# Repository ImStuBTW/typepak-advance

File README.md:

# TypePak Advance

The [TypePak Advance](https://github.com/ImStuBTW/typeboy-advance) is an update to my original [TypePak](https://github.com/ImStuBTW/typeboy_and_typepak/tree/main/typepak) design from 2023. The original idea for the concept was to put as many wireless keyboard components as possible inside of the shell of a Game Boy Advance cartridge. This allows you to more easily move the microcontroller between builds, but honestly it's primarily done for aesthetic reasons. Slapping a Game Boy cartridge port and cartridge onto the side of one's keyboard takes up a decent amount of space compared to a Pro Micro or a XIAO, but it does look neat. If you're iterating through designs rapidly, it does manage to cut down on some build considerations like where to put the LiPo battery.

The original TypePak design had a few flaws. It embedded an entire XIAO nRF52840 microcontroller onto the Game Boy cartridge breakout board. This simplified things on the design side, but complicated the assembly substantially. The XIAO's USB port needed to be exposed to flash new firmware and charge the TypePak's battery, so a large chunk needed to be cut out with a Dremel. The USB port was also fairly tall, and it had a nasty habit of crushing the integrated Sharp Memory Display as one tried to slide the enclosure together. In total 3 original TypePaks have been built, and only one managed to get a working display. Finally the pinout situation is less than ideal. The XIAO is famously limited on the amount of GPIO ports it has on offer, so the original TypePak leveraged a shift register to provide a few additional column pins. This worked well enough for split keyboards, but it's still not enough for unibody designs. In hindsight I *really* should have broken out the shift register's daisy-chain pin.

This v2 attempt is seeking to clean up a few lingering issues with the TypePak. The TypePak Advance's largest changes are:
- Leveraging a bare nRF52840 module to save space and give the display more space.
- Dropping the integrated USB port entirely in favor of breaking out those pins over the edge connector. No more cartridge shell modifications!
- More pins! The TypePak Advance has 23 GPIO pins exposed in total.
    - The nRF52840's high frequency pins are grouped together with the [VIK](https://github.com/sadekbaroudi/vik) keyboard extension standard in mind. After the VIK's SPI, I2C, RGB, and 2 GPI pins, the TypePak Advance still has 14 additional pins to work with.
- Features an always-on 3v3 pin and a toggle-able software controlled 3v3 pin to allow persistent and power conscious peripherals. 

To build a TypePak Advance compatible keyboard, one would need to include a Game Boy cartridge slot, a USB port for charging and data, a power switch, and a reset button.

The TypePak Advance leveraged the [nRFMicro](https://github.com/joric/nrfmicro) project for the basis of its schematic, and owes a great deal to the project's excellent documentation. Thanks y'all! The Game Boy Cartridge PCB designs are from [KiCAD-GamePaks](https://github.com/djedditt/kicad-gamepaks).

## Pinout

The TypePak Advance offers an indulgent 32 pins on its edge connector. A minimalist XAIO this is not. Nine of these pins are reserved for power, data, and board management features, but that still leaves you with 23 pins of GPIO. From left to right, you've got:

- The USB power and data pins. These pins need to be routed to a USB socket on the main keyboard PCB. (Most likely a USB-C port, but the pins can be put into a socket shape of your choice.)
- The Reset pin. Bridge this with the GND pin and your microcontroller will restart. Bridge it twice and the nRF52840 will boot into its flashing mode. This Reset pin and the GND should be wired up to a pushbutton on the main keyboard PCB.
- 14 GPIO pins. These pins are a mixture of the nRF52840's "Low Frequency" and "High Frequency" pins. The [nRFMicro Wiki](https://github.com/joric/nrfmicro/wiki/Pinout#low-drive-pins) has a good rundown, but essentially the high frequency pins are recommended for serial communication. Six of these pins can also be used for analog inputs.
- 9 additional serial and GPIO pins laid out in a similar order as to the [VIK](https://github.com/sadekbaroudi/vik) keyboard extension standard.
    - SPI's clock, input, output, and a chip select pin. The SCK and MISO pins have already been used by the built in Sharp Memory Display. These pins can be re-used for additional SPI devices, but shouldn't be used for general keyboard GPIO.
    - 2 general purpose pins.
    - An `RGB_Out` pin intended to be used for serial-addressable RGB LEDs. If the keyboard itself features addressable RGB LEDs, this pin should continue the end of the LED chain. If the keyboard does not feature an LED chain, it can be treated as the start of an RGB strand.
    - 2 pins for I2C serial communication.
- A software controllable 3v3 pin. Power to this pin can be shutoff via a MOSFET by ZMK so that power-hungry electronics such as LEDs do not drain your keyboard's battery life. It uses the same `EXT_VCC` functionality as the Nice!Nano and nRFMicro.
- An always-on 3v3 pin. This can be used for components which you will always want on, even when battery powered. Internally it's already giving power to the nRF52840 and the Sharp Memory Display.
- The battery pins. `BAT_OUT` is the line coming straight out of the LiPo battery. It needs to be connected to the VBAT pin in order to turn on the TypePak Advance. This should be done on the main keyboard PCB via a power switch.

## Open Considerations

I'm by no means an EE, and this is my first time working with a bare E73 nRF52840. Before I send this to the fab, I'm looking into the following topics. Consider this a to-do list of items I need to verify.

### Power

The nRFMicro has `VBAT`, `VBUS`, `nRF_VDD`, `EXT_VCC`, a `POWER_PIN`, and a `BATTERY_PIN`. I need to triple-check that I didn't get these mixed up anywhere.

Typically when working with batteries I put the switch onto the battery's `GND` lead so that the power pin isn't being as futzed with as much. The nRFMicro puts the switch on the power pin however, and I don't want to mess up any of the charging circuitry by accidentally having the battery's positive lead wired up when its not supposed to.

Breaking out the toggle-able `EXT_VCC` and always-on `nRF_VDD` looks worth it on paper, but it's been a bit since I've made a wireless keyboard. I'm not sure how many builds actually feature a mixture of components one would want powered up and powered down while wireless. Keeping the display on was my largest concern. I do have some spare GPIO pins I could break out if wanted an even number of pins on the board.

### Pins

Breaking out USB over an edge connector and running the data lines for a few centimeters has to be a pretty big no-no, right? The keyboard will be talking over Bluetooth most of the time. Maybe I should at least look into putting an ESD on the keyboard's port. I don't know if also putting one on the cartridge side would be a good idea too, but I'm starting to run out of room there.

I've never built a keyboard with VIK support in mind before, but I'm trying to future-proof this keyboard a bit. It'd be neat to power a trackball or trackpad via a TypePak. VIK's pinout is: `3V3, GND, SDA, SCL, RGB, 5V, GPIO1, MOSI, GPIO2, CS, MISO, and SCLK`. This is flipped on the TypePak so that when it's wired up to the connector, all the data pins would be in the correct order. The trick is that the TypePak doesn't have the 3v3, GND, or 5V pins mixed in with the rest. For the sake of maximizing the amount of GPIO, it would need to grab the GND off of the USB pinout, one of the 3V3 pinouts (with a selectable jumper pad if you wanted to get clever about it), and then... VBUS for the 5V pin? I don't know if this would actually meet the VIK spec, but it seems like most boards are focused on 3v3 devices. Also, shoot, I just realized VIK wanted one of those Analog In pins for its two GPIOs.

I was hoping to make a large VIK compatible unibody with this keyboard at some point, but there's surprisingly not enough pins to do it without a shift register. 12 columns and 5 rows is still 16 pins even if you optimize the matrix. It doesn't seem worth it to drop the `RESET` pin and rely on the keyboard firmware's software reset feature, and only offer the toggle-able 3V3. Shift register it is!

My understanding is that any high frequency pin can be used for SPI and I2C, but I should double-check that.

Again, this will be my first time working with a bare nRF52840 module, so we'll see how the placement on those programming pins goes. Wish me luck!

### Stray Thoughts

Earlier nRFMicro boards used a timing crystal between `P0.00` and `P0.01`. It would save a bit of battery life, but I'd need to find space for it and figure out how to enable it in the firmware.

I'm not using PCBA for this keyboard, so I bumped most of the 603 SMD components up to 805 variants that should be a little easier to hand solder.

Speaking of which, I still need to assemble a proper bill of materials for this build.

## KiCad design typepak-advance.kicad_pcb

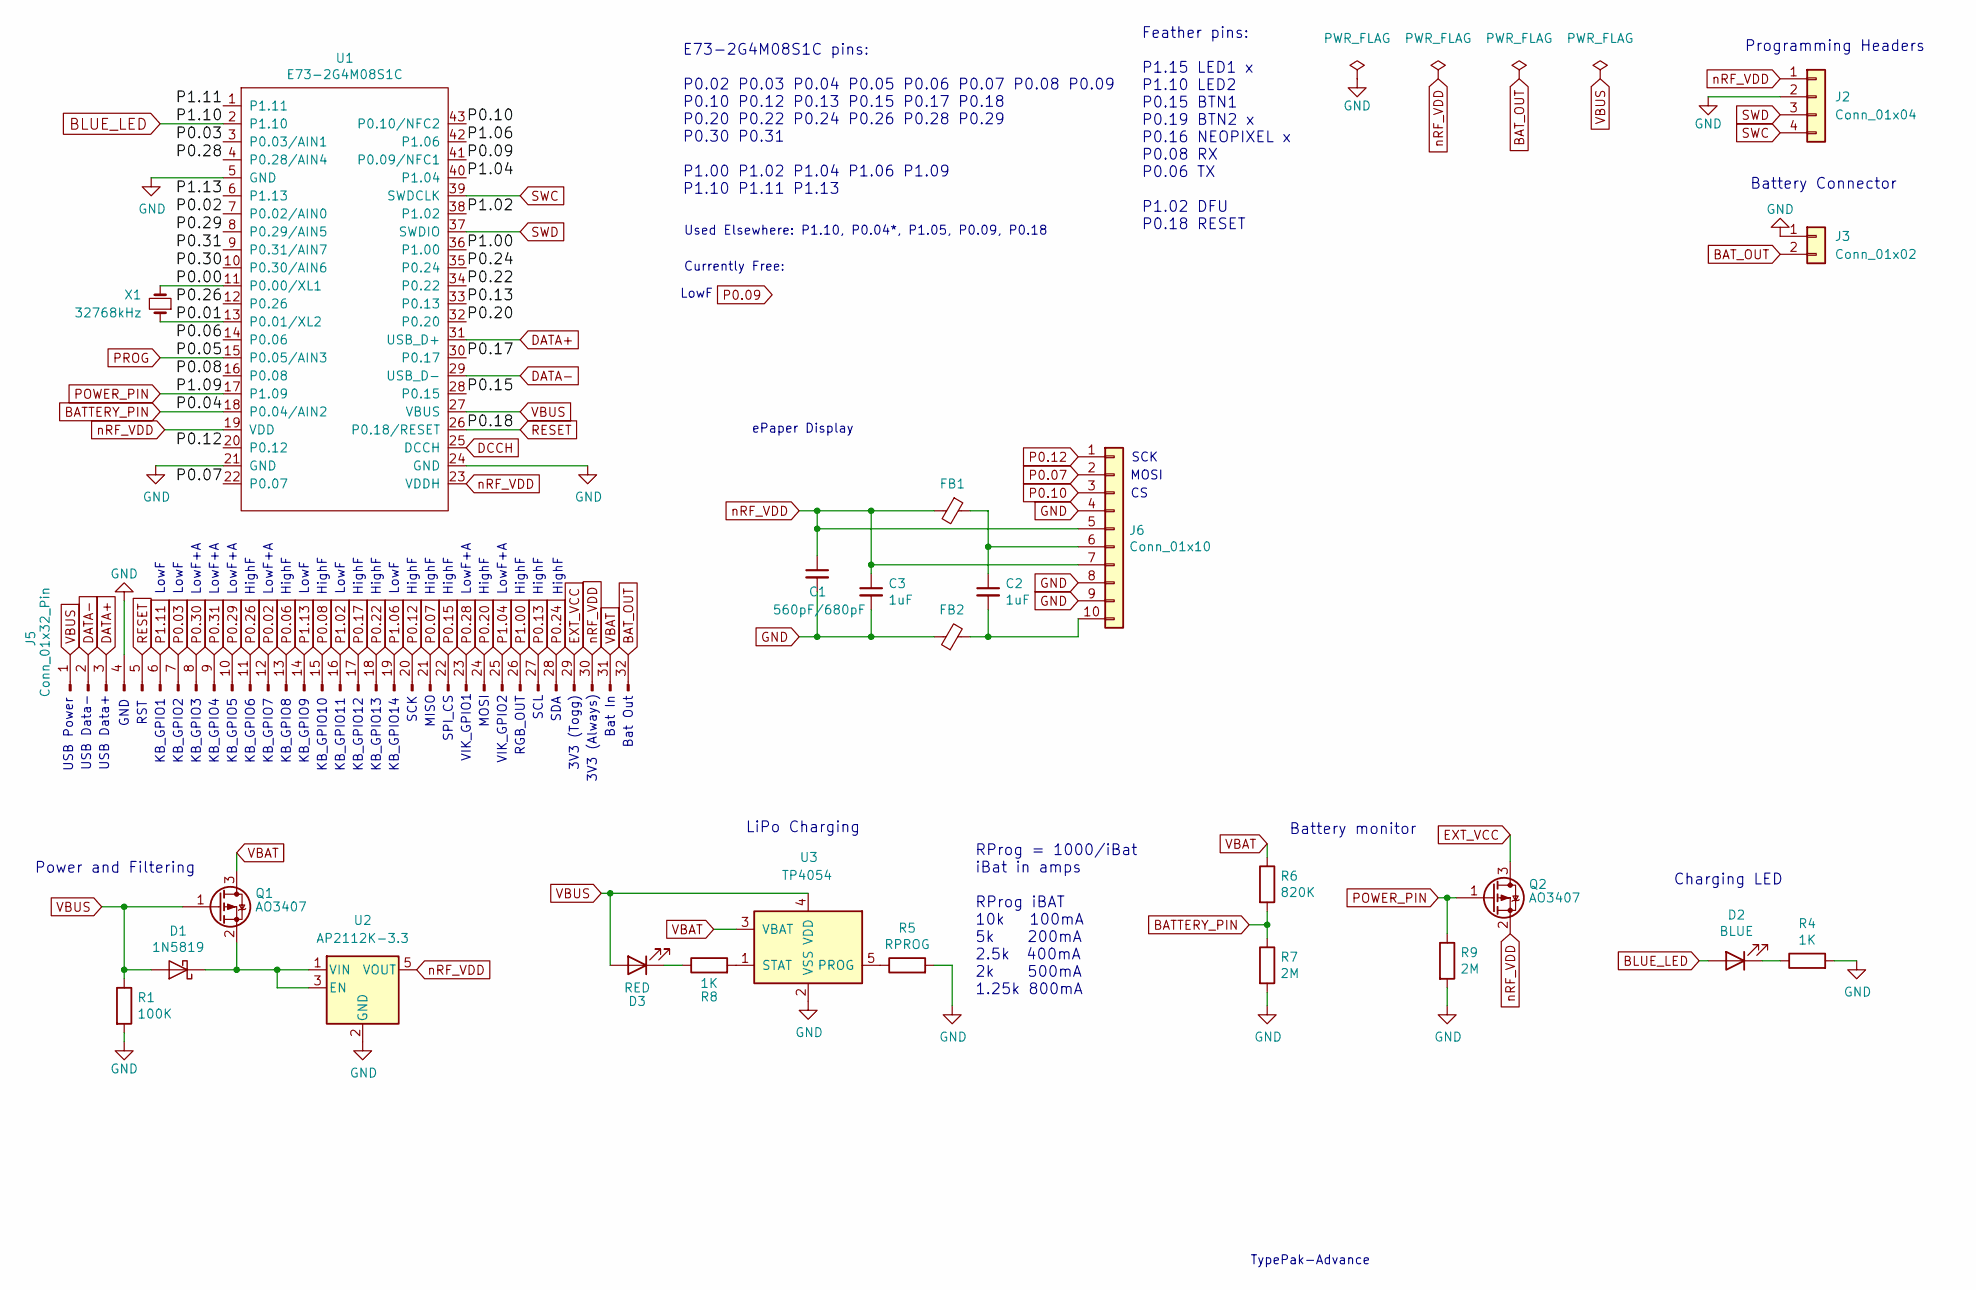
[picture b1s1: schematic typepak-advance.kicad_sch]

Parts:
C1: 560pF/680pF; C_0805_2012Metric_Pad1.18x1.45mm_HandSolder; LCSC C84721
C2, C3: 1uF; C_0805_2012Metric_Pad1.18x1.45mm_HandSolder; LCSC C15849
D1: 1N5819; D_SOD-123F
D2: BLUE; LED_0805_2012Metric_Pad1.15x1.40mm_HandSolder
D3: RED; LED_0805_2012Metric_Pad1.15x1.40mm_HandSolder
FB1, FB2: FerriteBead_Small; R_0805_2012Metric_Pad1.20x1.40mm_HandSolder
J2: Conn_01x04; connector_swd
J3: Conn_01x02
J5: Conn_01x32_Pin
J6: Conn_01x10; Hirose_FH12-10S-0.5SH_1x10-1MP_P0.50mm_Horizontal; LCSC C506791
Q1, Q2: AO3407; SOT-23_Handsoldering
R1: 100K; R_0805_2012Metric_Pad1.20x1.40mm_HandSolder
R4, R8: 1K; R_0805_2012Metric_Pad1.20x1.40mm_HandSolder
R5: RPROG; R_0805_2012Metric_Pad1.20x1.40mm_HandSolder
R6: 820K; R_0805_2012Metric_Pad1.20x1.40mm_HandSolder
R7, R9: 2M; R_0805_2012Metric_Pad1.20x1.40mm_HandSolder
U1: E73-2G4M08S1C; E73-2G4M08S1C-52840
U2: AP2112K-3.3; SOT-23-5_HandSoldering
U3: TP4054; SOT-23-5_HandSoldering
X1: 32768kHz

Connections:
/P0.00: U1.11 (P0.00/XL1), X1.2
/P0.01: U1.13 (P0.01/XL2), X1.1
BATTERY_PIN: R6.2, R7.1, U1.18 (P0.04/AIN2)
BAT_OUT: J3.2, J5.32
BLUE_LED: D2.2 (A), U1.2 (P1.10)
DATA+: J5.3, U1.31 (USB_D+)
DATA-: J5.2, U1.29 (USB_D-)
DCCH: U1.25 (DCCH)
EXT_VCC: J5.29, Q2.3 (D)
GND: C1.2, C3.2, FB2.1, J2.2, J3.1, J5.4, J6.4, J6.8, J6.9, R1.2, R4.2, R5.2, R7.2, R9.2, U1.5 (GND), U1.21 (GND), U1.24 (GND), U2.2 (GND), U3.2 (VSS)
unnamed: D1.1 (K), Q1.2 (S), U2.1 (VIN), U2.3 (EN)
unnamed: D2.1 (K), R4.1
unnamed: D3.1 (K), R8.1
unnamed: C2.1, FB1.1, J6.6
unnamed: C2.2, FB2.2, J6.10
unnamed: R5.1, U3.5 (PROG)
unnamed: R8.2, U3.1 (STAT)
P0.02: J5.12, U1.7 (P0.02/AIN0)
P0.03: J5.7, U1.3 (P0.03/AIN1)
P0.06: J5.13, U1.14 (P0.06)
P0.07: J5.21, J6.2, U1.22 (P0.07)
P0.08: J5.15, U1.16 (P0.08)
P0.09: U1.41 (P0.09/NFC1)
P0.10: J6.3, U1.43 (P0.10/NFC2)
P0.12: J5.20, J6.1, U1.20 (P0.12)
P0.13: J5.27, U1.33 (P0.13)
P0.15: J5.22, U1.28 (P0.15)
P0.17: J5.17, U1.30 (P0.17)
P0.20: J5.24, U1.32 (P0.20)
P0.22: J5.18, U1.34 (P0.22)
P0.24: J5.28, U1.35 (P0.24)
P0.26: J5.11, U1.12 (P0.26)
P0.28: J5.23, U1.4 (P0.28/AIN4)
P0.29: J5.10, U1.8 (P0.29/AIN5)
P0.30: J5.8, U1.10 (P0.30/AIN6)
P0.31: J5.9, U1.9 (P0.31/AIN7)
P1.00: J5.26, U1.36 (P1.00)
P1.02: J5.16, U1.38 (P1.02)
P1.04: J5.25, U1.40 (P1.04)
P1.06: J5.19, U1.42 (P1.06)
P1.11: J5.6, U1.1 (P1.11)
P1.13: J5.14, U1.6 (P1.13)
POWER_PIN: Q2.1 (G), R9.1, U1.17 (P1.09)
PROG: U1.15 (P0.05/AIN3)
RESET: J5.5, U1.26 (P0.18/RESET)
SWC: J2.4, U1.39 (SWDCLK)
SWD: J2.3, U1.37 (SWDIO)
VBAT: J5.31, Q1.3 (D), R6.1, U3.3 (VBAT)
VBUS: D1.2 (A), D3.2 (A), J5.1, Q1.1 (G), R1.1, U1.27 (VBUS), U3.4 (VDD)
nRF_VDD: C1.1, C3.1, FB1.2, J2.1, J5.30, J6.5, J6.7, Q2.2 (S), U1.19 (VDD), U1.23 (VDDH), U2.5 (VOUT)

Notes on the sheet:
SDA
MOSI
VIK_GPIO2
LowF
TypePak-Advance
KB_GPIO10
USB Data-
LowF+A
HighF
SCL
RProg = 1000/iBat iBat in amps RProg iBAT 10k 100mA 5k 200mA 2.5k 400mA 2k 500mA 1.25k 800mA
VIK_GPIO1
KB_GPIO13
3V3 (Togg)
KB_GPIO5
KB_GPIO1
KB_GPIO7
SCK
Feather pins: P1.15 LED1 x P1.10 LED2 P0.15 BTN1 P0.19 BTN2 x P0.16 NEOPIXEL x P0.08 RX P0.06 TX P1.02 DFU P0.18 RESET
KB_GPIO4
KB_GPIO9
USB Power
RGB_OUT
KB_GPIO2
MISO
KB_GPIO6
Currently Free:
Bat In
ePaper Display
KB_GPIO14
KB_GPIO12
Programming Headers
Bat Out
KB_GPIO8
USB Data+
Battery Connector
LiPo Charging
Power and Filtering
GND
SPI_CS

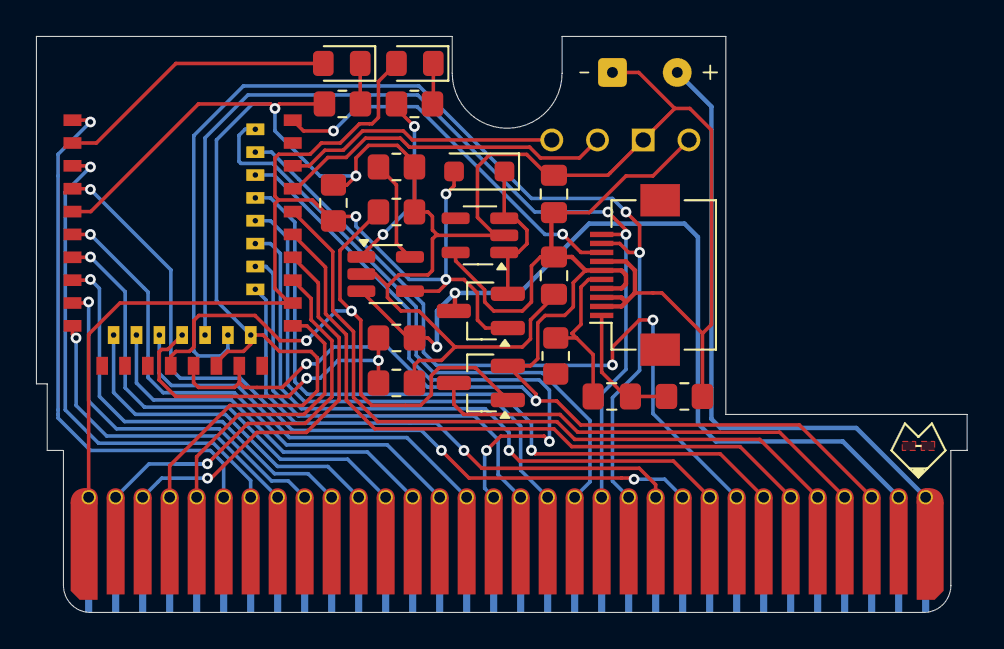
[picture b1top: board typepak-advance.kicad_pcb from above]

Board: 2 copper layers, 51.7 x 32.0 mm, 24 parts (0 on the bottom side), 45 nets.

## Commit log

2025-06-15 Initial Commit.
2025-06-15 Fixed images.
2025-06-15 Removed to-do item.
2025-06-15 Cleaned up traces.
2025-06-15 README updates.
2025-07-06 Updated to hand-solder footprints.
